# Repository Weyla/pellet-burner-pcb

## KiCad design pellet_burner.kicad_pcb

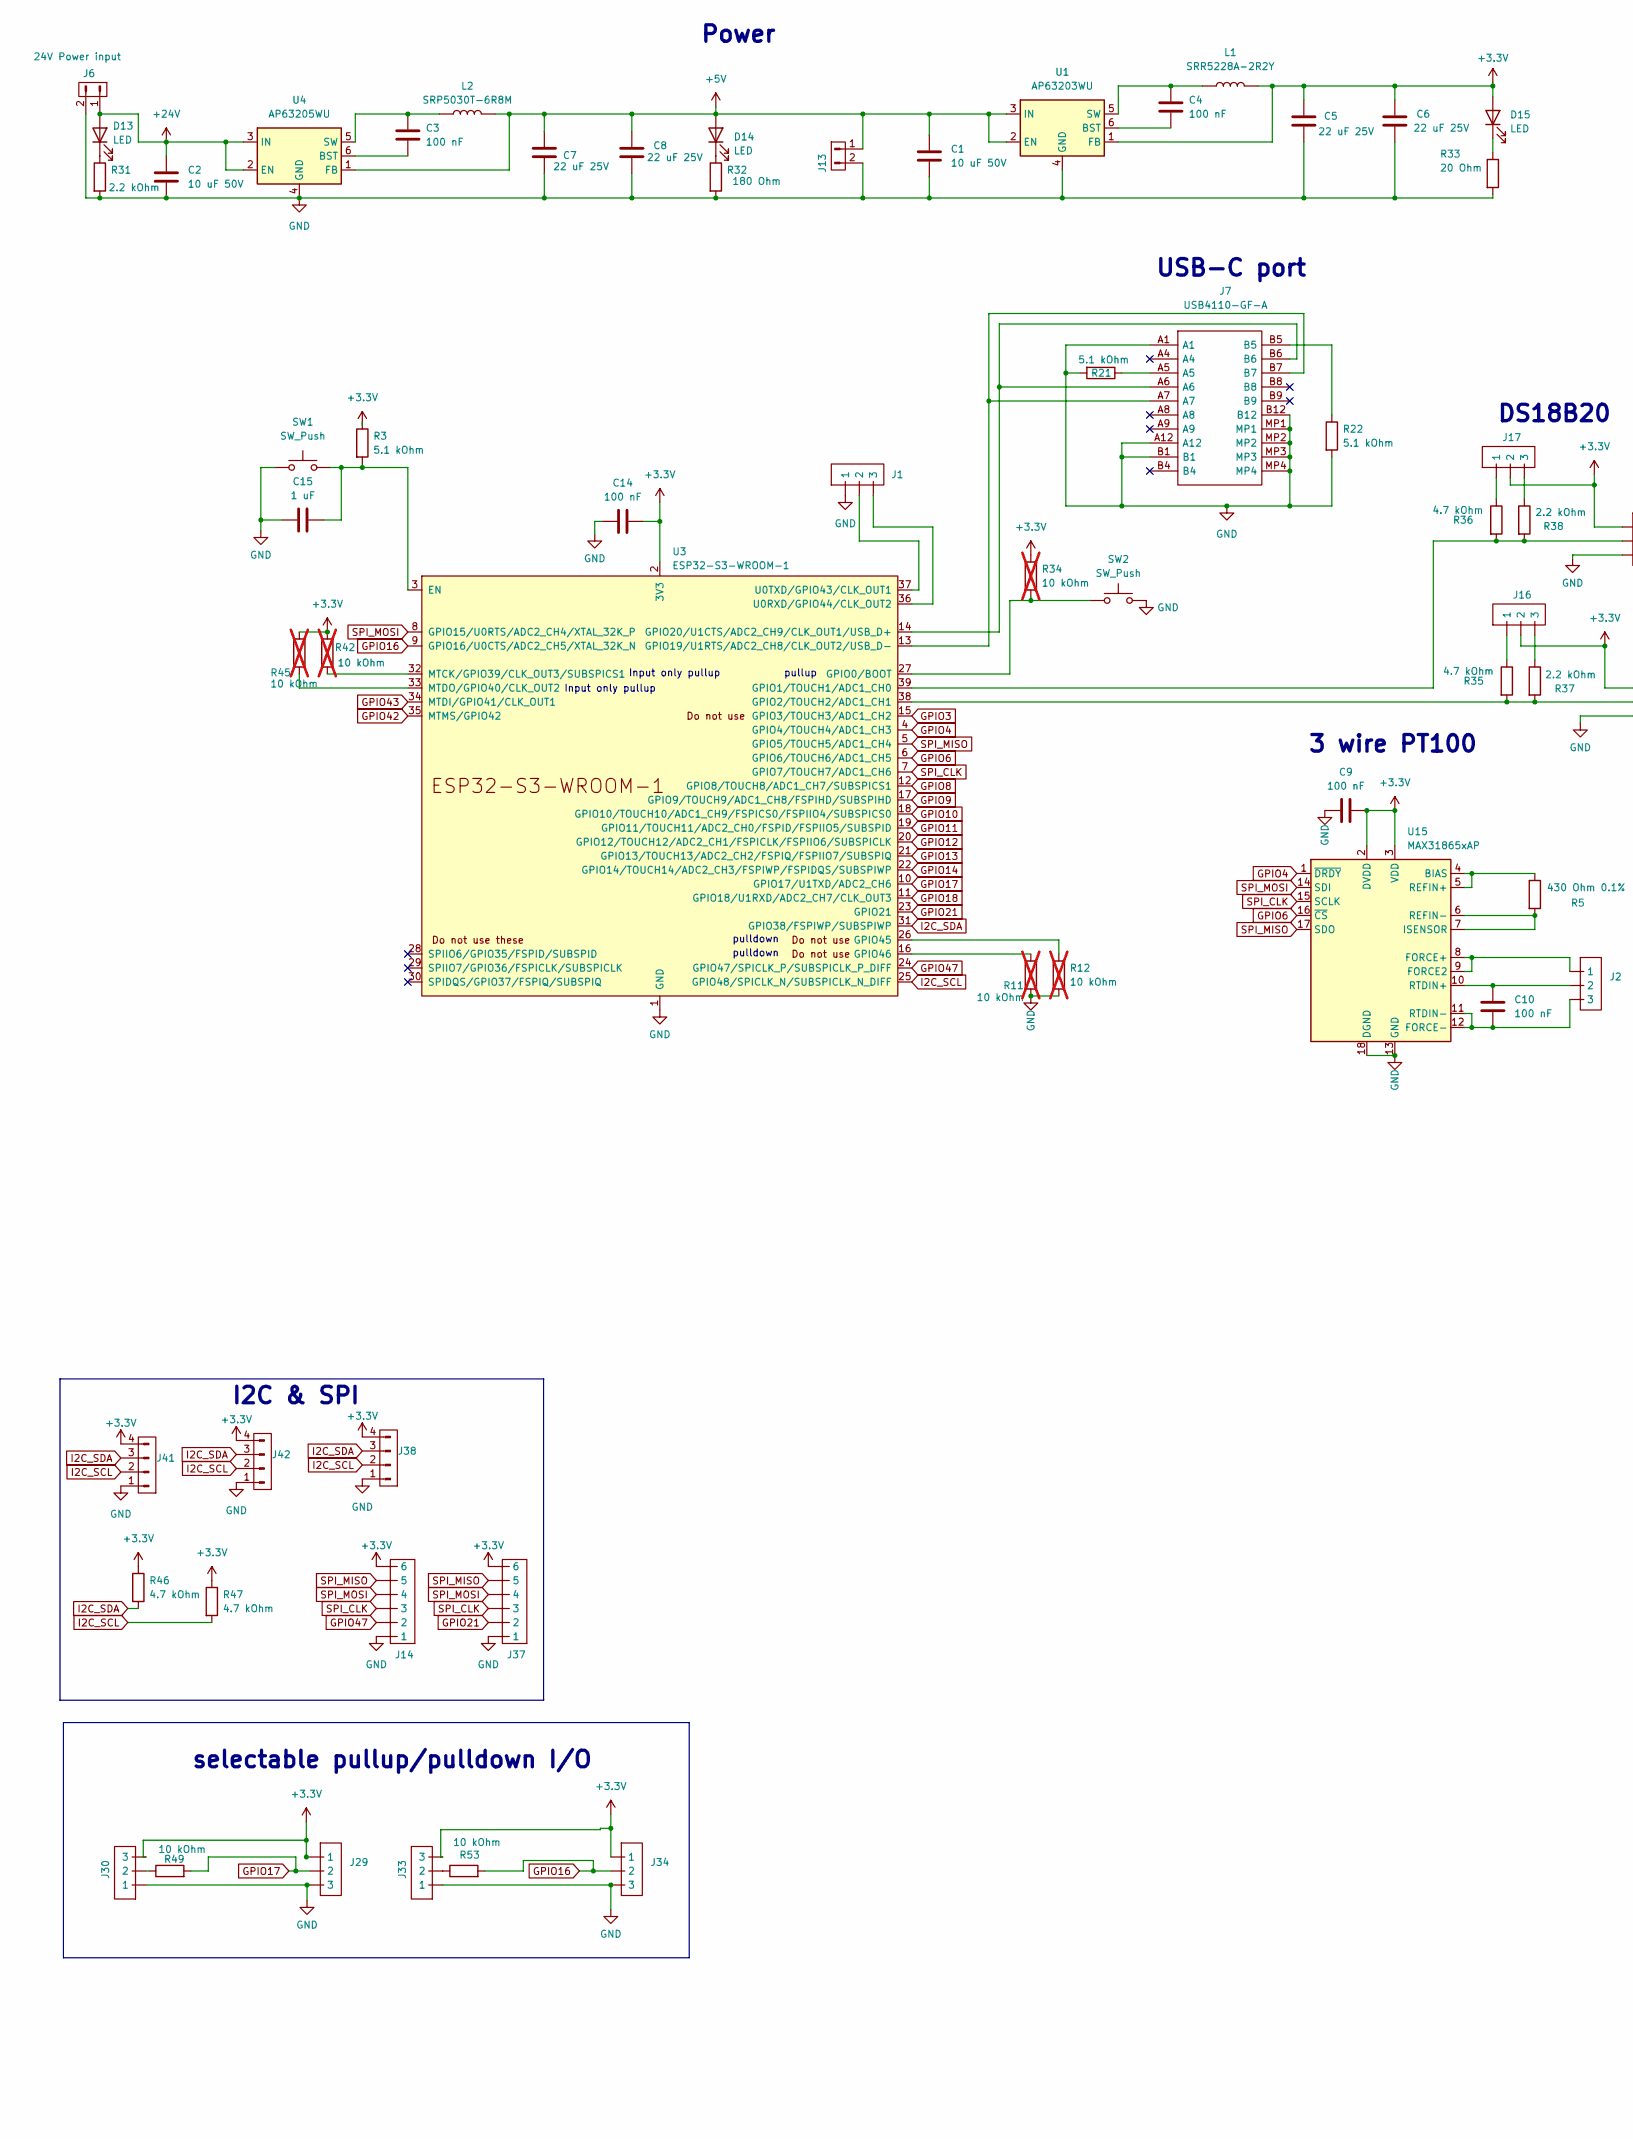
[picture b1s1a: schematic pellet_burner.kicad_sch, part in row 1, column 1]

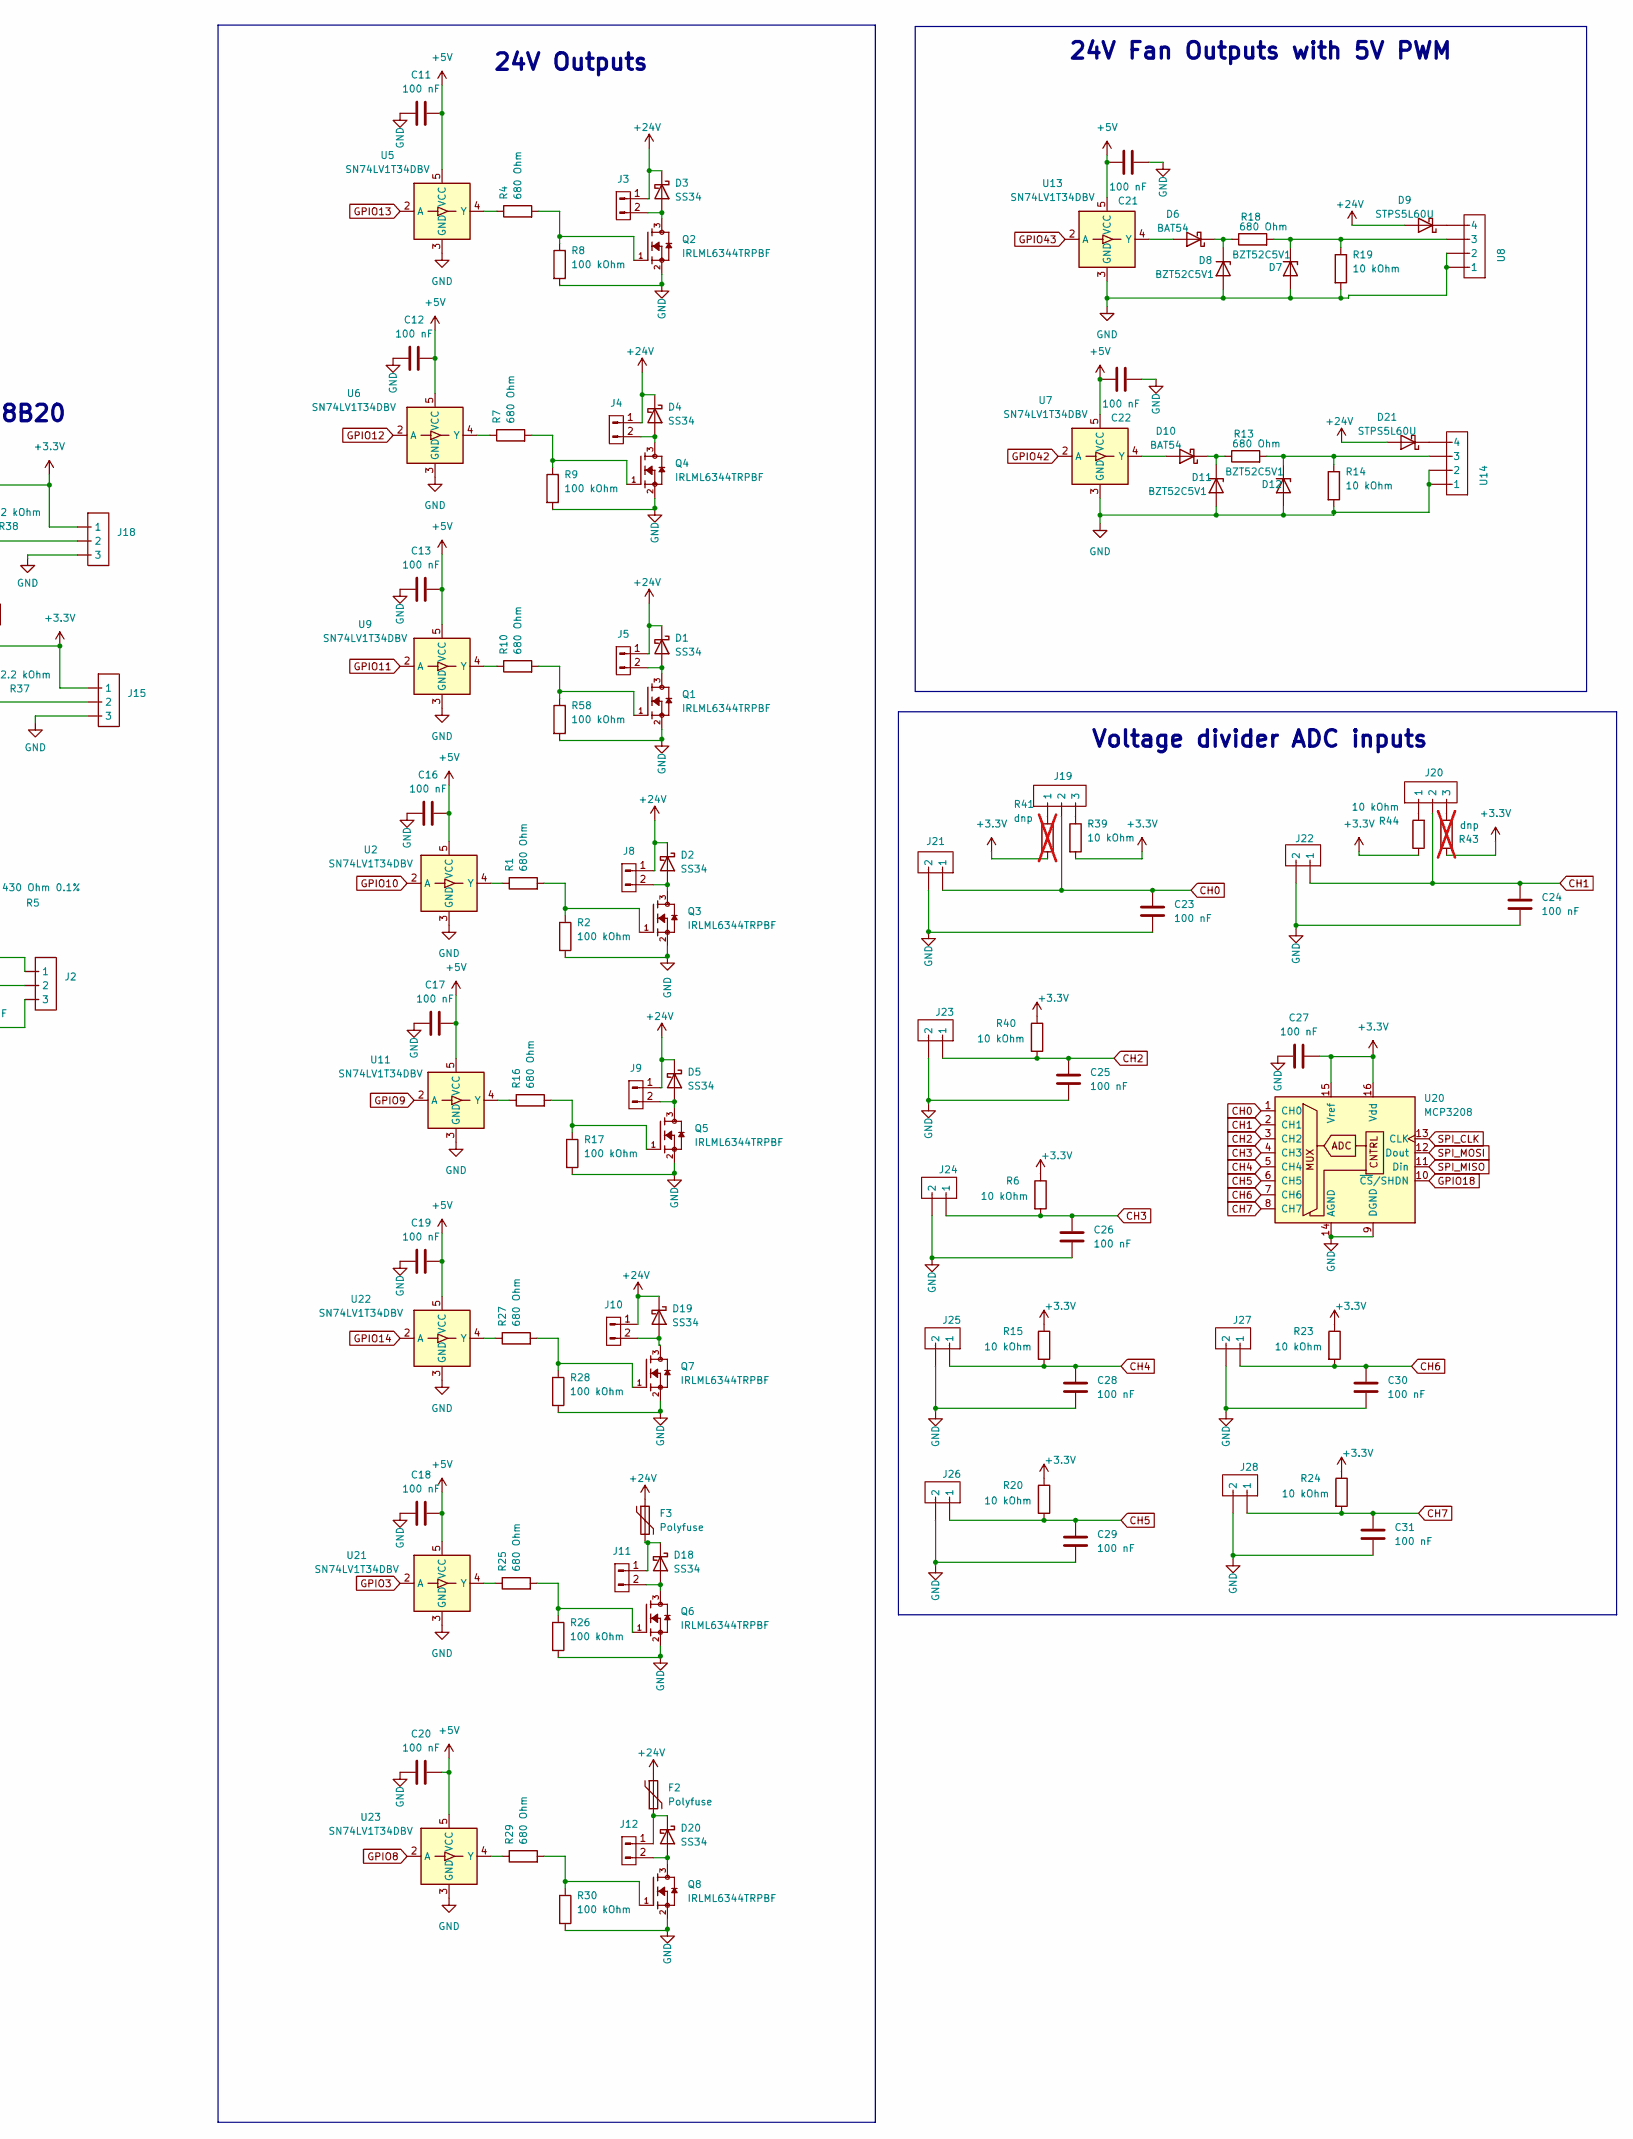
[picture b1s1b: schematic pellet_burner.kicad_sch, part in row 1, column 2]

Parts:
C1, C2: 10 uF 50V; C_1206_3216Metric; LCSC C13585
C3, C4: 100 nF; C_0805_2012Metric; LCSC C49678
C5, C6, C7, C8: 22 uF 25V; C_1206_3216Metric; LCSC C12891
C9, C10, C11, C12, C13, C14, C16, C17, C18, C19, C20, C21, C22, C23, C24, C25, C26, C27, C28, C29, C30, C31: 100 nF; C_0805_2012Metric
C15: 1 uF; C_0805_2012Metric
D1, D2, D3, D4, D5, D18, D19, D20: SS34; D_SMA
D6, D10: BAT54; SOT-23-3
D7, D8, D11, D12: BZT52C5V1; D_SOD-123F
D9, D21: STPS5L60U; D_SMB
D13, D14, D15: LED; LED_0805_2012Metric
F2, F3: Polyfuse; Fuse_1210_3225Metric
J1, J2, J15, J18, J29, J34: JST_XH_B3B-XH-AM_1x03_P2.50mm_Vertical
J3, J4, J5, J8, J9, J10, J11, J12: JST_XH_1x2_vertical
J6: 24V Power input; TerminalBlock_MaiXu_MX126-5.0-02P_1x02_P5.00mm
J7: USB4110-GF-A; USB4110GFA; Mouser Part Number 640-USB4110-GF-A
J13: 5v; TerminalBlock_MaiXu_MX126-5.0-02P_1x02_P5.00mm
J14, J37: JST_XH_B6B-XH-A_1x06_P2.50mm_Vertical
J16, J17, J19, J20, J30, J33: PinHeader_1x03_P2.54mm_Vertical
J21, J22, J23, J24, J25, J26, J27, J28: JST_XH_B2B-XH-AM_1x02_P2.50mm_Vertical
J38, J41, J42: JST_XH_B4B-XH-A_1x04_P2.50mm_Vertical
L1: SRR5228A-2R2Y; SRR5228A
L2: SRP5030T-6R8M; SRP5030T
Q1, Q2, Q3, Q4, Q5, Q6, Q7, Q8: IRLML6344TRPBF; TSOT-23; PARTREV December 19, 2014
R1, R4, R7, R10, R13, R16, R18, R25, R27, R29: 680 Ohm; R_0805_2012Metric
R2, R8, R9, R17, R26, R28, R30, R58: 100 kOhm; R_0805_2012Metric
R3, R21, R22: 5.1 kOhm; R_0805_2012Metric
R5: 430 Ohm 0.1%; R_0805_2012Metric
R6, R14, R15, R19, R20, R23, R24, R39, R40, R44, R49, R53: 10 kOhm; R_0805_2012Metric
R11, R12, R34, R42, R45: 10 kOhm; R_0805_2012Metric; not fitted
R31, R37, R38: 2.2 kOhm; R_0805_2012Metric
R32: 180 Ohm; R_0805_2012Metric
R33: 20 Ohm; R_0805_2012Metric
R35, R36, R46, R47: 4.7 kOhm; R_0805_2012Metric
R41, R43: dnp; R_0805_2012Metric; not fitted
SW1, SW2: SW_Push; 3x4x2 switch
U1: AP63203WU; TSOT-23-6; LCSC C780769
U2, U5, U6, U7, U9, U11, U13, U21, U22, U23: SN74LV1T34DBV; SOT-23-5
U3: ESP32-S3-WROOM-1; ESP32-S3-WROOM-1U
U4: AP63205WU; TSOT-23-6
U8, U14: JST_XH_B4B-XH-A_1x04_P2.50mm_Vertical
U15: MAX31865xAP; SSOP-20_5.3x7.2mm_P0.65mm
U20: MCP3208; SOIC-16_3.9x9.9mm_P1.27mm

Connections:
+3.3V: C5.1, C6.1, C9.1, C14.1, C27.1, D15.2 (A), J14.6, J15.1, J16.2, J17.2, J18.1, J29.1, J30.3, J33.3, J34.1, J37.6, J38.4, J41.4, J42.4, L1.2, R3.1, R6.1, R15.1, R20.1, R23.1, R24.1, R34.1, R39.2, R40.1, R41.2, R42.1, R43.1, R44.1, R45.1, R46.1, R47.1, U1.1 (FB), U3.2 (3V3), U15.2 (DVDD), U15.3 (VDD), U20.15 (Vref), U20.16 (Vdd)
+5V: C1.1, C7.1, C8.1, C11.1, C12.1, C13.1, C16.1, C17.1, C18.1, C19.1, C20.1, C21.1, C22.1, D14.2 (A), J13.1, L2.2, U1.2 (EN), U1.3 (IN), U2.5 (VCC), U4.1 (FB), U5.5 (VCC), U6.5 (VCC), U7.5 (VCC), U9.5 (VCC), U11.5 (VCC), U13.5 (VCC), U21.5 (VCC), U22.5 (VCC), U23.5 (VCC)
+24V: C2.1, D1.1 (K), D2.1 (K), D3.1 (K), D4.1 (K), D5.1 (K), D9.2 (A), D13.2 (A), D19.1 (K), D21.2 (A), F2.1, F3.1, J3.1, J4.1, J5.1, J6.1, J8.1, J9.1, J10.1, U4.2 (EN), U4.3 (IN)
CH0: C23.1, J19.2, J21.1, U20.1 (CH0)
CH1: C24.1, J20.2, J22.1, U20.2 (CH1)
CH2: C25.1, J23.1, R40.2, U20.3 (CH2)
CH3: C26.1, J24.1, R6.2, U20.4 (CH3)
CH4: C28.1, J25.1, R15.2, U20.5 (CH4)
CH5: C29.1, J26.1, R20.2, U20.6 (CH5)
CH6: C30.1, J27.1, R23.2, U20.7 (CH6)
CH7: C31.1, J28.1, R24.2, U20.8 (CH7)
GND: C1.2, C2.2, C5.2, C6.2, C7.2, C8.2, C9.2, C11.2, C12.2, C13.2, C14.2, C15.2, C16.2, C17.2, C18.2, C19.2, C20.2, C21.2, C22.2, C23.2, C24.2, C25.2, C26.2, C27.2, C28.2, C29.2, C30.2, C31.2, D7.2 (A), D8.2 (A), D11.2 (A), D12.2 (A), J1.1, J6.2, J7.A1, J7.A12, J7.B1, J7.B12, J7.MP1, J7.MP2, J7.MP3, J7.MP4, J13.2, J14.1, J15.3, J18.3, J21.2, J22.2, J23.2, J24.2, J25.2, J26.2, J27.2, J28.2, J29.3, J30.1, J33.1, J34.3, J37.1, J38.1, J41.1, J42.1, Q1.2, Q2.2, Q3.2, Q4.2, Q5.2, Q6.2, Q7.2, Q8.2, R2.2, R8.2, R9.2, R11.2, R12.2, R14.2, R17.2, R19.2, R21.2, R22.2, R26.2, R28.2, R30.2, R31.2, R32.2, R33.2, R58.2, SW1.1, SW2.2, U1.4 (GND), U2.3 (GND), U3.1 (GND), U3.40 (GND), U3.41 (GND), U4.4 (GND), U5.3 (GND), U6.3 (GND), U7.3 (GND), U8.1, U8.2, U9.3 (GND), U11.3 (GND), U13.3 (GND), U14.1, U14.2, U15.13 (GND), U15.18 (DGND), U15.19 (GND), U20.9 (DGND), U20.14 (AGND), U21.3 (GND), U22.3 (GND), U23.3 (GND)
GPIO3: U3.15 (GPIO3/TOUCH3/ADC1_CH2), U21.2 (A)
GPIO4: U3.4 (GPIO4/TOUCH4/ADC1_CH3), U15.1 (~DRDY)
GPIO6: U3.6 (GPIO6/TOUCH6/ADC1_CH5), U15.16 (~CS)
GPIO8: U3.12 (GPIO8/TOUCH8/ADC1_CH7/SUBSPICS1), U23.2 (A)
GPIO9: U3.17 (GPIO9/TOUCH9/ADC1_CH8/FSPIHD/SUBSPIHD), U11.2 (A)
GPIO10: U2.2 (A), U3.18 (GPIO10/TOUCH10/ADC1_CH9/FSPICS0/FSPIIO4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)
GPIO11: U3.19 (GPIO11/TOUCH11/ADC2_CH0/FSPID/FSPIIO5/S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), U9.2 (A)
GPIO12: U3.20 (GPIO12/TOUCH12/ADC2_CH1/FSPICLK/FSPIIO6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), U6.2 (A)
GPIO13: U3.21 (GPIO13/TOUCH13/ADC2_CH2/FSPIQ/FSPIIO7/S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), U5.2 (A)
GPIO14: U3.22 (GPIO14/TOUCH14/ADC2_CH3/FSPIWP/FSPIDQS/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), U22.2 (A)
GPIO16: J34.2, R53.2, U3.9 (GPIO16/U0CTS/ADC2_CH5/XTAL_32K_N)
GPIO17: J29.2, R49.2, U3.10 (GPIO17/U1TXD/ADC2_CH6)
GPIO18: U3.11 (GPIO18/U1RXD/ADC2_CH7/CLK_OUT3), U20.10 (~CS/SHDN)
GPIO21: J37.2, U3.23 (GPIO21)
GPIO42: U3.35 (MTMS/GPIO42), U7.2 (A)
GPIO43: U3.34 (MTDI/GPIO41/CLK_OUT1), U13.2 (A)
GPIO47: J14.2, U3.24 (GPIO47/SPICLK_P/SUBSPICLK_P_DIFF)
I2C_SCL: J38.2, J41.2, J42.2, R47.2, U3.25 (GPIO48/SPICLK_N/SUBSPICLK_N_DIFF)
I2C_SDA: J38.3, J41.3, J42.3, R46.2, U3.31 (GPIO38/FSPIWP/SUBSPIWP)
unnamed: D1.2 (A), J5.2, Q1.3
unnamed: D2.2 (A), J8.2, Q3.3
unnamed: D3.2 (A), J3.2, Q2.3
unnamed: D4.2 (A), J4.2, Q4.3
unnamed: D5.2 (A), J9.2, Q5.3
unnamed: D6.2 (A), U13.4 (Y)
unnamed: D6.1 (K), D8.1 (K), R18.1
unnamed: D7.1 (K), R18.2, R19.1, U8.3
unnamed: D9.1 (K), U8.4
unnamed: D10.2 (A), U7.4 (Y)
unnamed: D10.1 (K), D11.1 (K), R13.1
unnamed: D12.1 (K), R13.2, R14.1, U14.3
unnamed: D13.1 (K), R31.1
unnamed: D14.1 (K), R32.1
unnamed: D15.1 (K), R33.1
unnamed: D18.2 (A), J11.2, Q6.3
unnamed: D18.1 (K), F3.2, J11.1
unnamed: D19.2 (A), J10.2, Q7.3
unnamed: D20.2 (A), J12.2, Q8.3
unnamed: D20.1 (K), F2.2, J12.1
unnamed: D21.1 (K), U14.4
unnamed: J7.A5, R21.1
unnamed: J7.B5, R22.1
unnamed: J16.1, R35.1
unnamed: J16.3, R37.1
unnamed: J17.1, R36.1
unnamed: J17.3, R38.1
unnamed: J19.1, R41.1
unnamed: J19.3, R39.1
unnamed: J20.1, R44.2
unnamed: J20.3, R43.2
unnamed: J30.2, R49.1
unnamed: J33.2, R53.1
unnamed: Q1.1, R10.2, R58.1
unnamed: Q2.1, R4.2, R8.1
unnamed: Q3.1, R1.2, R2.1
unnamed: Q4.1, R7.2, R9.1
unnamed: Q5.1, R16.2, R17.1
unnamed: Q6.1, R25.2, R26.1
unnamed: Q7.1, R27.2, R28.1
unnamed: Q8.1, R29.2, R30.1
unnamed: C4.2, U1.6 (BST)
unnamed: C4.1, L1.1, U1.5 (SW)
unnamed: R1.1, U2.4 (Y)
unnamed: C15.1, R3.2, SW1.2, U3.3 (EN)
unnamed: R34.2, SW2.1, U3.27 (GPIO0/BOOT)
unnamed: J18.2, R36.2, R38.2, U3.39 (GPIO1/TOUCH1/ADC1_CH0)
unnamed: J15.2, R35.2, R37.2, U3.38 (GPIO2/TOUCH2/ADC1_CH1)
unnamed: J7.A7, J7.B7, U3.13 (GPIO19/U1RTS/ADC2_CH8/CLK_OUT2/USB_D-)
unnamed: J7.A6, J7.B6, U3.14 (GPIO20/U1CTS/ADC2_CH9/CLK_OUT1/USB_D+)
unnamed: R12.1, U3.26 (GPIO45)
unnamed: R11.1, U3.16 (GPIO46)
unnamed: R42.2, U3.32 (MTCK/GPIO39/CLK_OUT3/SUBSPICS1)
unnamed: R45.2, U3.33 (MTDO/GPIO40/CLK_OUT2)
unnamed: J1.3, U3.36 (U0RXD/GPIO44/CLK_OUT2)
unnamed: J1.2, U3.37 (U0TXD/GPIO43/CLK_OUT1)
unnamed: C3.2, U4.6 (BST)
unnamed: C3.1, L2.1, U4.5 (SW)
unnamed: R4.1, U5.4 (Y)
unnamed: R7.1, U6.4 (Y)
unnamed: R10.1, U9.4 (Y)
unnamed: R16.1, U11.4 (Y)
unnamed: R5.1, U15.4 (BIAS), U15.5 (REFIN+)
unnamed: J2.1, U15.8 (FORCE+), U15.9 (FORCE2)
unnamed: C10.1, J2.3, U15.11 (RTDIN-), U15.12 (FORCE-)
unnamed: R5.2, U15.6 (REFIN-), U15.7 (ISENSOR)
unnamed: C10.2, J2.2, U15.10 (RTDIN+)
unnamed: R25.1, U21.4 (Y)
unnamed: R27.1, U22.4 (Y)
unnamed: R29.1, U23.4 (Y)
SPI_CLK: J14.3, J37.3, U3.7 (GPIO7/TOUCH7/ADC1_CH6), U15.15 (SCLK), U20.13 (CLK)
SPI_MISO: J14.5, J37.5, U3.5 (GPIO5/TOUCH5/ADC1_CH4), U15.17 (SDO), U20.11 (Din)
SPI_MOSI: J14.4, J37.4, U3.8 (GPIO15/U0RTS/ADC2_CH4/XTAL_32K_P), U15.14 (SDI), U20.12 (Dout)

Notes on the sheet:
I2C & SPI
pulldown
3 wire PT100
Power
Voltage divider ADC inputs
Input only pullup
USB-C port
DS18B20
pullup
24V Fan Outputs with 5V PWM
selectable pullup/pulldown I/O
24V Outputs

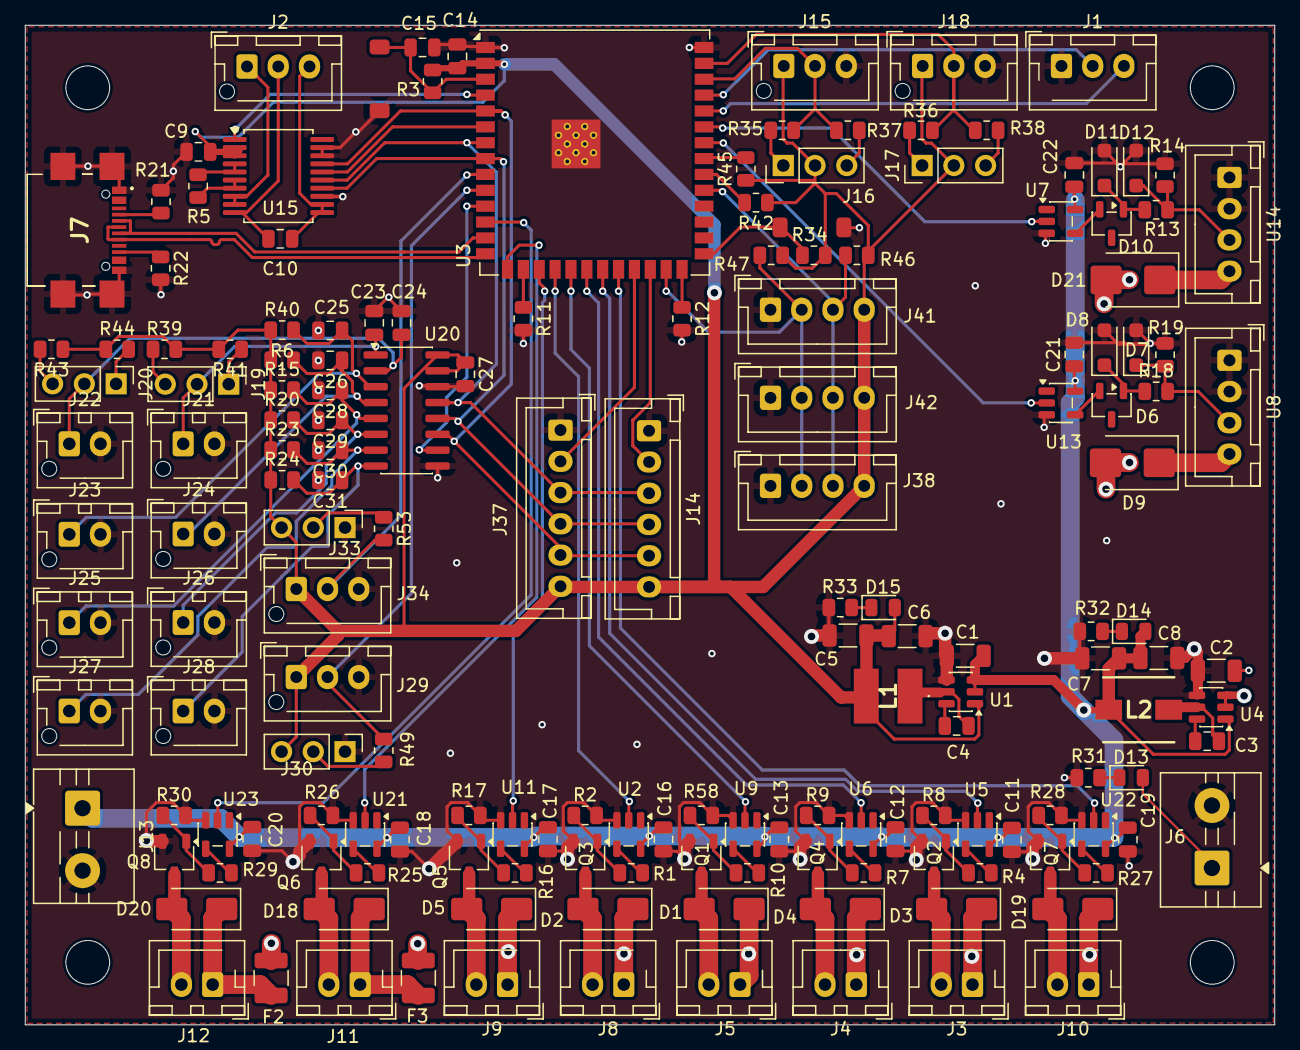
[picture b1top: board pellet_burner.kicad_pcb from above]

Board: 4 copper layers, 100.0 x 80.0 mm, 167 parts (0 on the bottom side), 104 nets.

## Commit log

2026-01-04 First upload
2026-01-04 folder change
